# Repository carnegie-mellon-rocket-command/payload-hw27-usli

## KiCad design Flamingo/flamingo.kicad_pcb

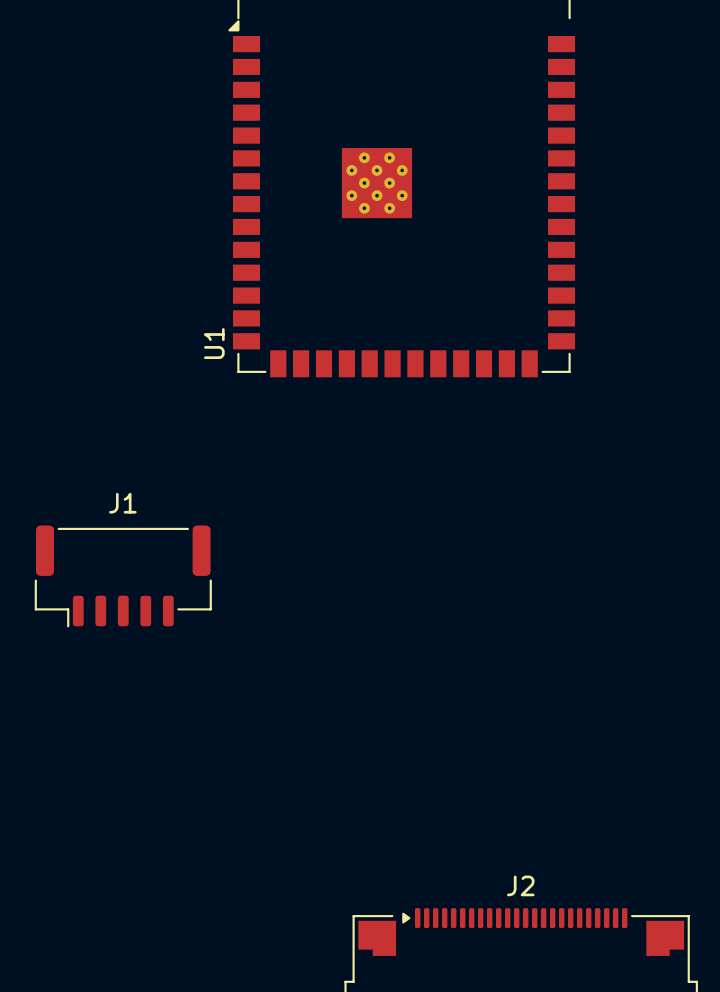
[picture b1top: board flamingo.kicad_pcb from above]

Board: 2 copper layers, 3 parts (0 on the bottom side), 19 nets, no tracks yet.

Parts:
J1: STA-M020X; JST_GH_BM05B-GHS-TBT_1x05-1MP_P1.25mm_Vertical
J2: Conn_01x24; Amphenol_F32Q-1A7x1-11024_1x24-1MP_P0.5mm_Horizontal
U1: ESP32-S3-WROOM-1-N16R8; ESP32-S3-WROOM-1

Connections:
/ESP32-S3 core/CAM_HREF: J2.9, U1.18 (IO10)
/ESP32-S3 core/CAM_PCLK: J2.17, U1.16 (IO46)
/ESP32-S3 core/CAM_RST: J2.6, U1.6 (IO6)
/ESP32-S3 core/CAM_SCL: J2.5, U1.5 (IO5)
/ESP32-S3 core/CAM_SDA: J2.3, U1.4 (IO4)
/ESP32-S3 core/CAM_VSYNC: J2.7, U1.17 (IO9)
/ESP32-S3 core/CAM_XCLK: J2.13, U1.21 (IO13)
/ESP32-S3 core/CAM_Y2: J2.19, U1.8 (IO15)
/ESP32-S3 core/CAM_Y3: J2.21, U1.9 (IO16)
/ESP32-S3 core/CAM_Y4: J2.22, U1.10 (IO17)
/ESP32-S3 core/CAM_Y5: J2.20, U1.11 (IO18)
/ESP32-S3 core/CAM_Y6: J2.18, U1.12 (IO8)
/ESP32-S3 core/CAM_Y7: J2.16, U1.13 (USB_D-)
/ESP32-S3 core/CAM_Y8: J2.14, U1.14 (USB_D+)
/ESP32-S3 core/CAM_Y9: J2.12, U1.15 (IO3)
/ESP32-S3 core/LASER_RX: J1.4, U1.38 (IO2)
/ESP32-S3 core/LASER_TX: J1.3, U1.39 (IO1)
GND: J1.1, J2.15
unnamed: U1.1 (GND), U1.40 (GND), U1.41 (GND)

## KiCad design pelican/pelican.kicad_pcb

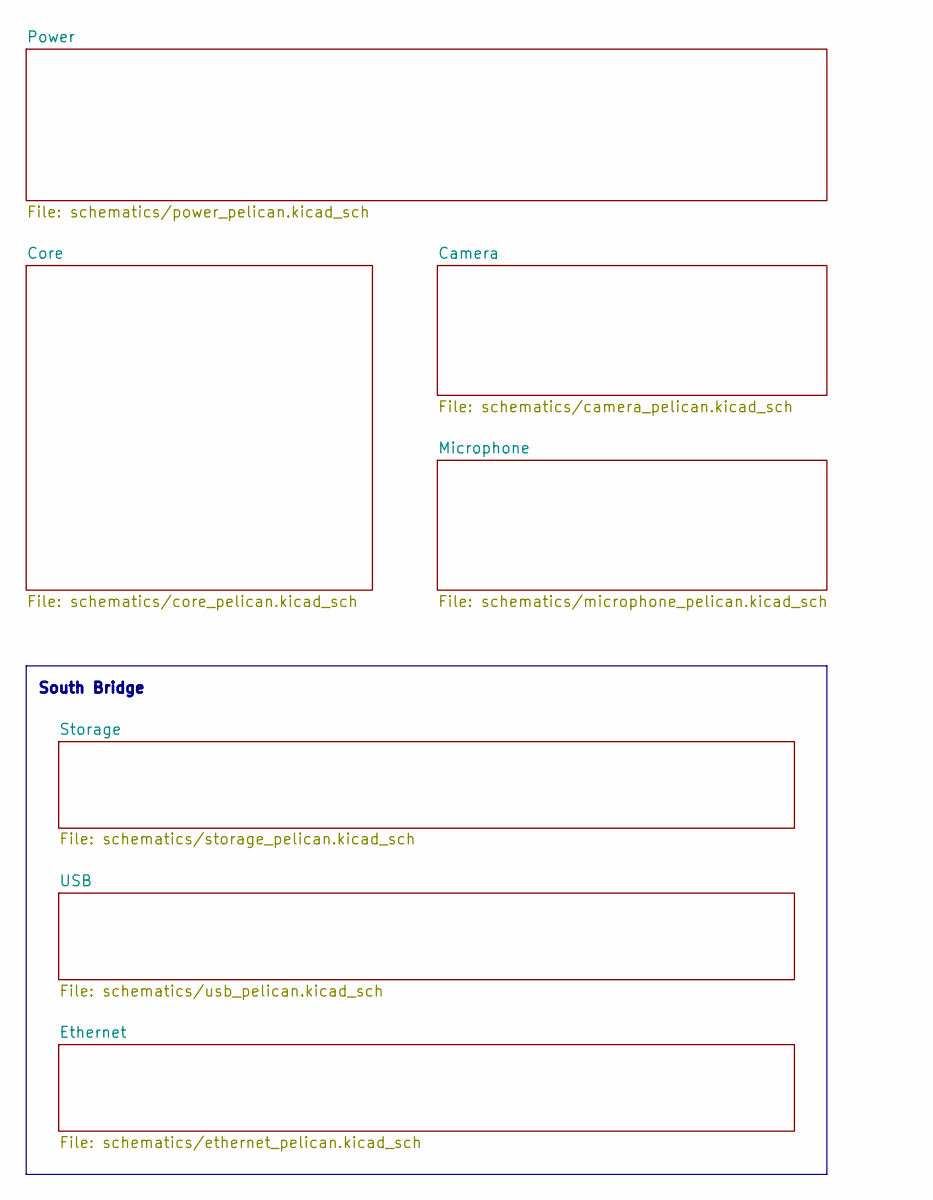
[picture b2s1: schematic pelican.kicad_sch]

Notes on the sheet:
South Bridge

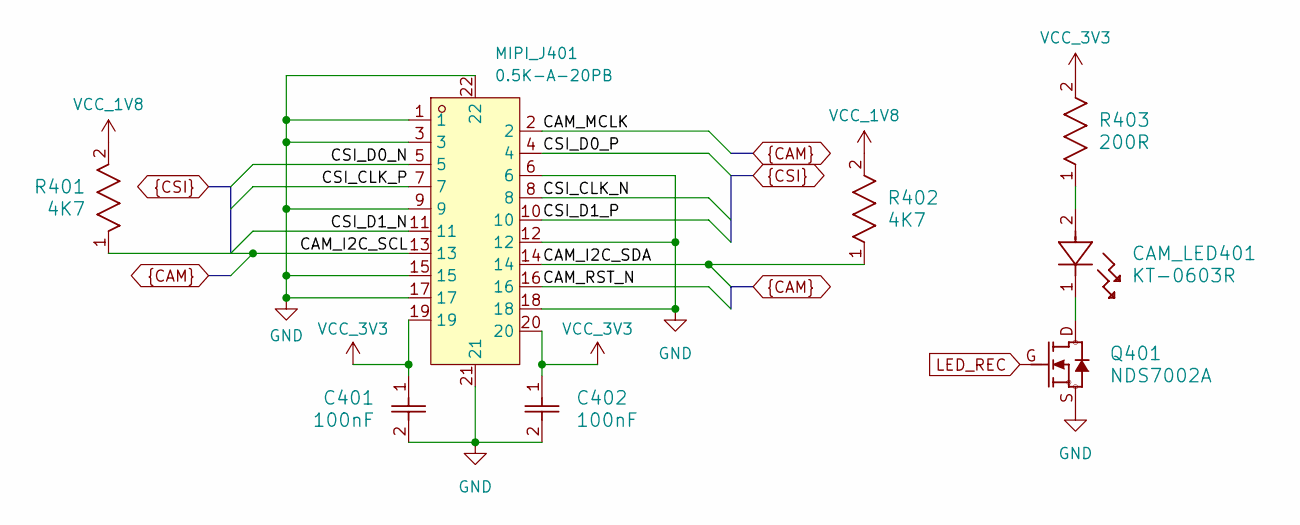
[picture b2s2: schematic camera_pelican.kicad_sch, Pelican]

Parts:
C401, C402: 100nF; C_GRM155R71C104KA88D; LCSC Part # C1525
CAM_LED401: KT-0603R; LED_LTST-C193KRKT-5A; LCSC Part # C2286
MIPI_J401: 0.5K-A-20PB; J_0.5K-A-20PB; MPN 0.5K-A-20PB; LCSC Part C2914144
Q401: NDS7002A; Q_NDS7002A; LCSC Part # C74715
R401, R402: 4K7; R_RC0402FR; LCSC Part # C25900
R403: 200R; R_RC0402FR; LCSC Part # C25087

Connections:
CAM_I2C_SCL: MIPI_J401.13, R401.1; also elsewhere on the board
CAM_I2C_SDA: MIPI_J401.14, R402.1; also elsewhere on the board
CAM_MCLK: MIPI_J401.2; also elsewhere on the board
CAM_RST_N: MIPI_J401.16; also elsewhere on the board
CSI_CLK_N: MIPI_J401.8; also elsewhere on the board
CSI_CLK_P: MIPI_J401.7; also elsewhere on the board
CSI_D0_N: MIPI_J401.5; also elsewhere on the board
CSI_D0_P: MIPI_J401.4; also elsewhere on the board
CSI_D1_N: MIPI_J401.11; also elsewhere on the board
CSI_D1_P: MIPI_J401.10; also elsewhere on the board
GND: C401.2, C402.2, MIPI_J401.1, MIPI_J401.3, MIPI_J401.6, MIPI_J401.9, MIPI_J401.12, MIPI_J401.15, MIPI_J401.17, MIPI_J401.18, MIPI_J401.21, MIPI_J401.22, Q401.S; also elsewhere on the board
LED_REC: Q401.G; also elsewhere on the board
unnamed: CAM_LED401.1, Q401.D
unnamed: CAM_LED401.2, R403.1
VCC_1V8: R401.2, R402.2; also elsewhere on the board
VCC_3V3: C401.1, C402.1, MIPI_J401.19, MIPI_J401.20, R403.2; also elsewhere on the board

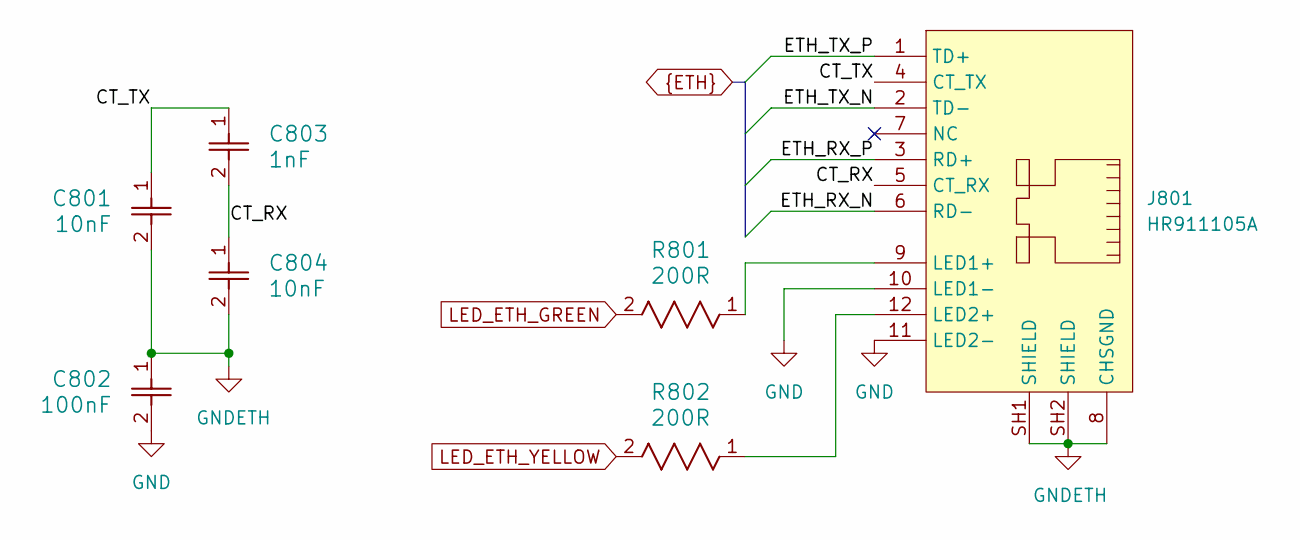
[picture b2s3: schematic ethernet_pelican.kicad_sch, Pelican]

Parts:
C801, C804: 10nF; C_CL05B103KO5NNNC; MPN CL05B103KO5NNNC; LCSC Part # C15195
C802: 100nF; C_GRM155R71C104KA88D; LCSC Part # C1525
C803: 1nF; C_CC0603CG100V102JN; MPN CC0603CG100V102JN; LCSC Part # C53084479
J801: HR911105A; J_HR911105A_TH; MPN HR911105A; LCSC Part C12074
R801, R802: 200R; R_RC0402FR; LCSC Part # C25087

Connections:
/Ethernet/CT_RX: C803.2, C804.1, J801.5 (CT_RX)
/Ethernet/CT_TX: C801.1, C803.1, J801.4 (CT_TX)
ETH_RX_N: J801.6 (RD-); also elsewhere on the board
ETH_RX_P: J801.3 (RD+); also elsewhere on the board
ETH_TX_N: J801.2 (TD-); also elsewhere on the board
ETH_TX_P: J801.1 (TD+); also elsewhere on the board
GND: C802.2, J801.10 (LED1-), J801.11 (LED2-); also elsewhere on the board
GNDETH: C801.2, C802.1, C804.2, J801.8 (CHSGND), J801.SH1 (SHIELD), J801.SH2 (SHIELD)
LED_ETH_GREEN: R801.2; also elsewhere on the board
LED_ETH_YELLOW: R802.2; also elsewhere on the board
unnamed: J801.9 (LED1+), R801.1
unnamed: J801.12 (LED2+), R802.1

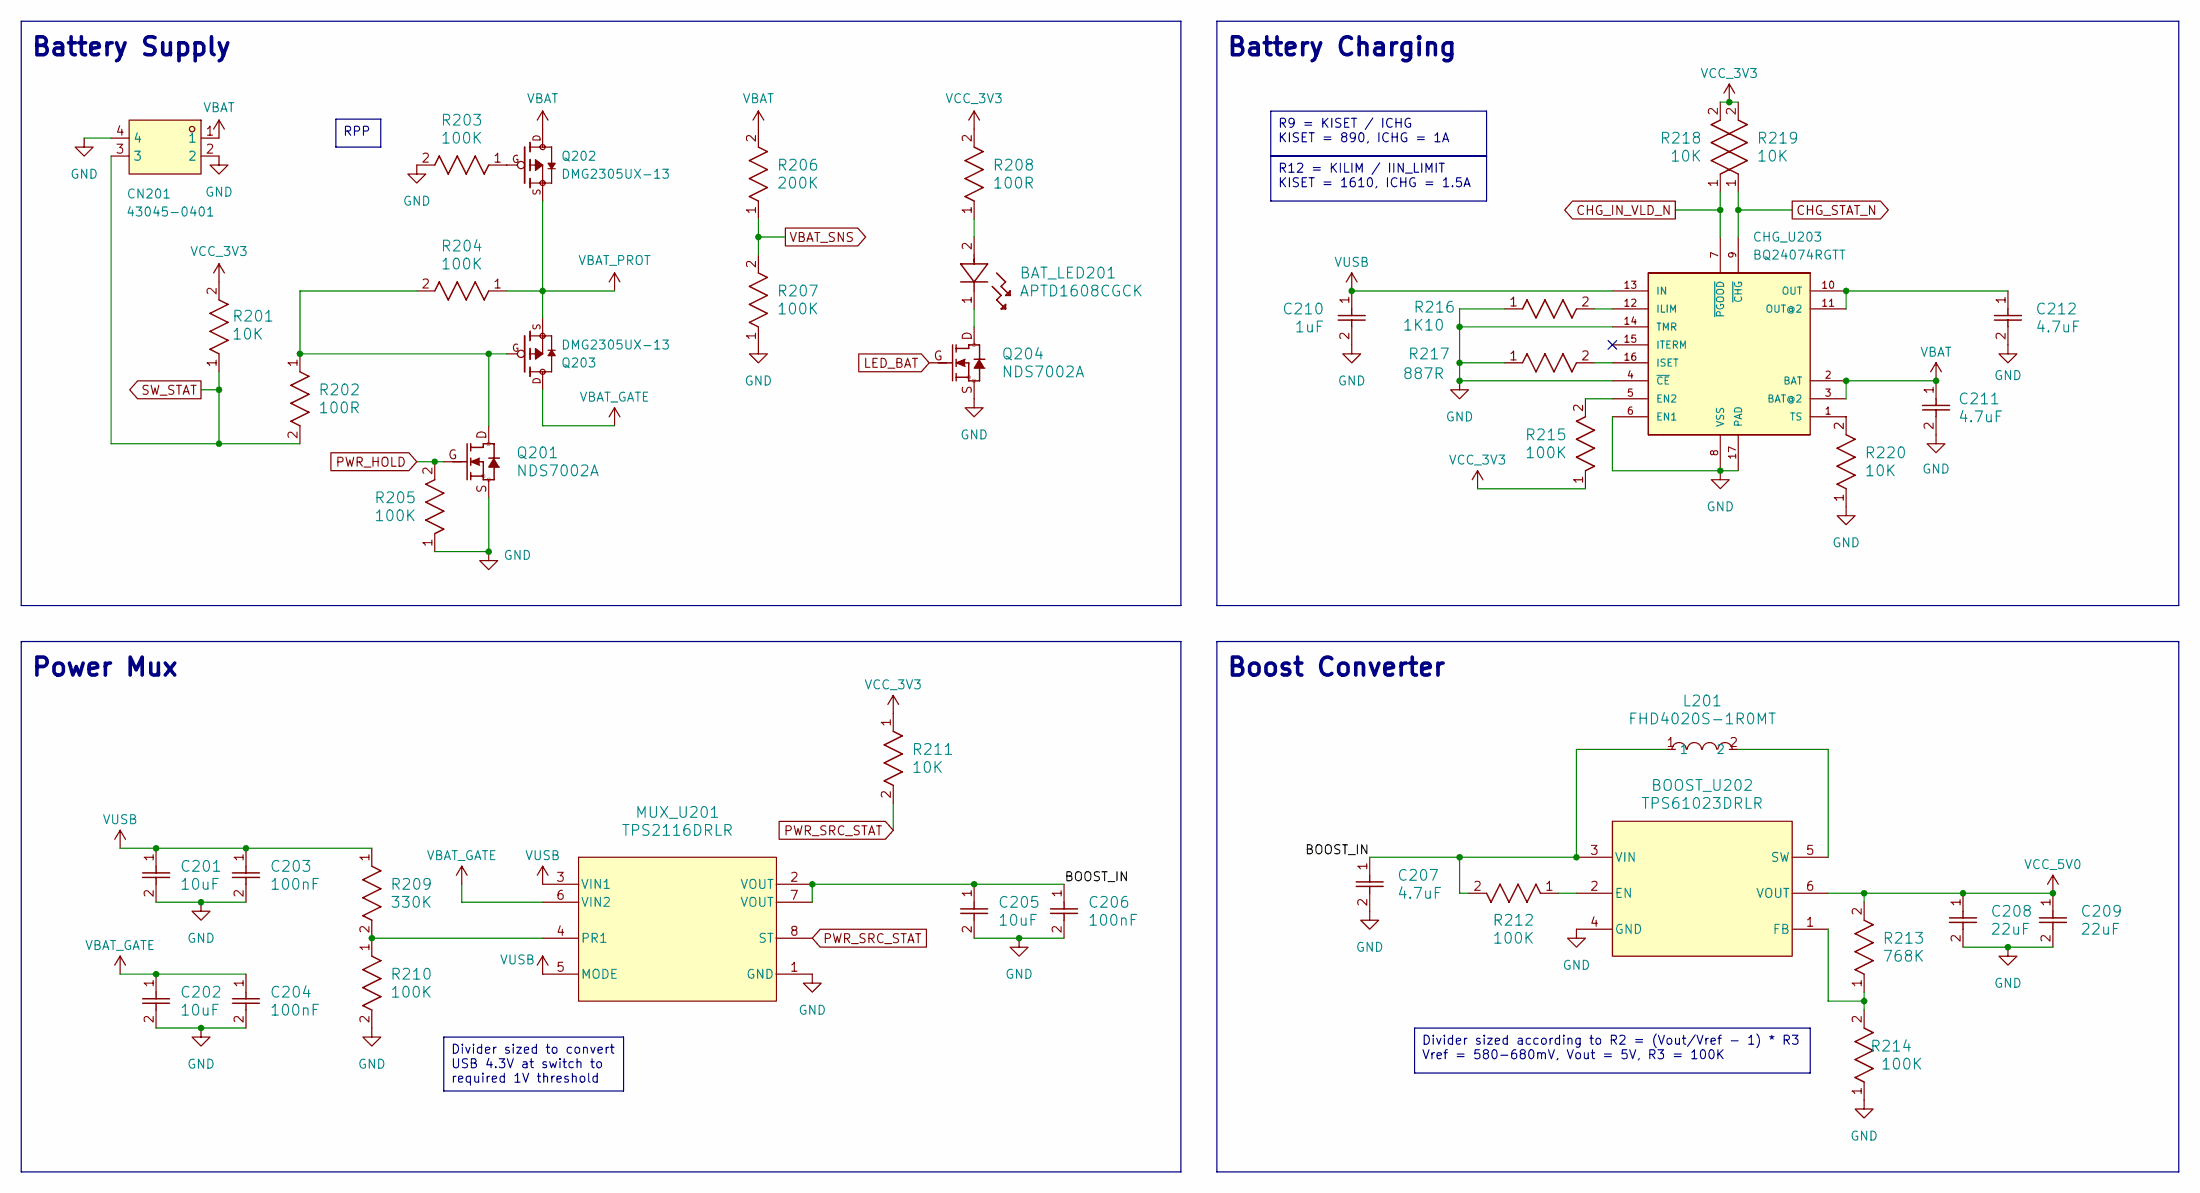
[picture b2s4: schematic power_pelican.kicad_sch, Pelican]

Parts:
BAT_LED201: APTD1608CGCK; LED_LTST-C193KGKT-5A; LCSC Part # C5121471
BOOST_U202: TPS61023DRLR; U_TPS61023DRLR; LCSC Part # C919459
C201, C202, C205: 10uF; C_GRM155R61A106ME11D; LCSC Part # C408132
C203, C204, C206: 100nF; C_GRM155R71C104KA88D; LCSC Part # C1525
C207, C211, C212: 4.7uF; C_GRM188R61A475KE15D; LCSC Part # C19666
C208, C209: 22uF; C_GRM188R61A226ME15D; LCSC Part # C84419
C210: 1uF; C_GRM155R61A105KE15D; LCSC Part # C52923
CHG_U203: BQ24074RGTT; U_BQ24074RGTT; LCSC Part # C2861252
CN201: 43045-0401; J_43045-0401_2x02_RA; MPN 430450401; LCSC Part C585880
L201: FHD4020S-1R0MT; L_FHD4020S-1R0MT; MPN FHD4020S-1R0MT; LCSC Part # C602028
MUX_U201: TPS2116DRLR; U_TPS2116DRLR; LCSC Part # C3235557
Q201, Q204: NDS7002A; Q_NDS7002A; LCSC Part # C74715
Q202, Q203: DMG2305UX-13; Q_DMG2305UX-13; PARTREV 09/2018; LCSC Part # C144153
R201, R211, R218, R219, R220: 10K; R_RC0402FR; LCSC Part # C25744
R202, R208: 100R; R_RC0402FR; LCSC Part # C25076
R203, R204, R205, R207, R210, R212, R214, R215: 100K; R_RC0402FR; LCSC Part # C25741
R206: 200K; R_RC0402FR; LCSC Part # C25764
R209: 330K; R_RC0402FR; LCSC Part # C25778
R213: 768K; R_RC0402FR; LCSC Part # C273722
R216: 1K10; R_RC0402FR; LCSC Part # C25860
R217: 887R; R_RC0402FR; LCSC Part # C477810

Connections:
/Power/BOOST_IN: BOOST_U202.3 (VIN), C205.1, C206.1, C207.1, L201.1, MUX_U201.2 (VOUT), MUX_U201.7 (VOUT), R212.2
CHG_IN_VLD_N: CHG_U203.7 (~PGOOD), R218.1; also elsewhere on the board
CHG_STAT_N: CHG_U203.9 (~CHG), R219.1; also elsewhere on the board
GND: BOOST_U202.4 (GND), C201.2, C202.2, C203.2, C204.2, C205.2, C206.2, C207.2, C208.2, C209.2, C210.2, C211.2, C212.2, CHG_U203.4 (~CE), CHG_U203.6 (EN1), CHG_U203.8 (VSS), CHG_U203.14 (TMR), CHG_U203.17 (PAD), CN201.2, CN201.4, MUX_U201.1 (GND), Q201.S, Q204.S, R203.2, R205.1, R207.1, R210.2, R214.1, R216.1, R217.1, R220.1; also elsewhere on the board
LED_BAT: Q204.G; also elsewhere on the board
unnamed: BAT_LED201.1, Q204.D
unnamed: BAT_LED201.2, R208.1
unnamed: BOOST_U202.2 (EN), R212.1
unnamed: BOOST_U202.1 (FB), R213.1, R214.2
unnamed: BOOST_U202.5 (SW), L201.2
unnamed: CHG_U203.5 (EN2), R215.2
unnamed: CHG_U203.12 (ILIM), R216.2
unnamed: CHG_U203.16 (ISET), R217.2
unnamed: C212.1, CHG_U203.10 (OUT), CHG_U203.11 (OUT@2)
unnamed: CHG_U203.1 (TS), R220.2
unnamed: MUX_U201.4 (PR1), R209.2, R210.1
unnamed: Q201.D, Q203.G, R202.1, R204.2
unnamed: Q202.G, R203.1
unnamed: Q202.S, Q203.S, R204.1
PWR_HOLD: Q201.G, R205.2; also elsewhere on the board
PWR_SRC_STAT: MUX_U201.8 (ST), R211.2; also elsewhere on the board
SW_STAT: CN201.3, R201.1, R202.2; also elsewhere on the board
VBAT: C211.1, CHG_U203.2 (BAT), CHG_U203.3 (BAT@2), CN201.1, Q202.D, R206.2
VBAT_SNS: R206.1, R207.2; also elsewhere on the board
VCC_3V3: R201.2, R208.2, R211.1, R215.1, R218.2, R219.2; also elsewhere on the board
VCC_5V0: BOOST_U202.6 (VOUT), C208.1, C209.1, R213.2; also elsewhere on the board
VUSB: C201.1, C203.1, C210.1, CHG_U203.13 (IN), MUX_U201.3 (VIN1), MUX_U201.5 (MODE), R209.1; also elsewhere on the board

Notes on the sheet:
Battery Charging
Power Mux
Battery Supply
Boost Converter
Divider sized according to R2 = (Vout/Vref - 1) * R3 Vref = 580-680mV, Vout = 5V, R3 = 100K
R12 = KILIM / IIN_LIMIT KISET = 1610, ICHG = 1.5A
R9 = KISET / ICHG KISET = 890, ICHG = 1A
Divider sized to convert USB 4.3V at switch to required 1V threshold
RPP

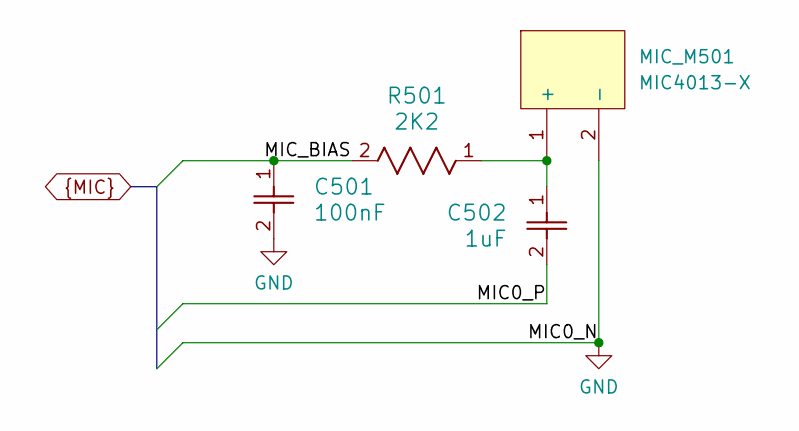
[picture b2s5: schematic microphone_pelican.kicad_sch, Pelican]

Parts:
C501: 100nF; C_GRM155R71C104KA88D; LCSC Part # C1525
C502: 1uF; C_GRM155R61A105KE15D; LCSC Part # C52923
MIC_M501: MIC4013-X; M_MIC4013-X; MPN MIC4013-X; LCSC Part # C49118137
R501: 2K2; R_RC0402FR; LCSC Part # C25879

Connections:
GND: C501.2, MIC_M501.2 (-); also elsewhere on the board
MIC0_P: C502.2; also elsewhere on the board
MIC_BIAS: C501.1, R501.2; also elsewhere on the board
unnamed: C502.1, MIC_M501.1 (+), R501.1

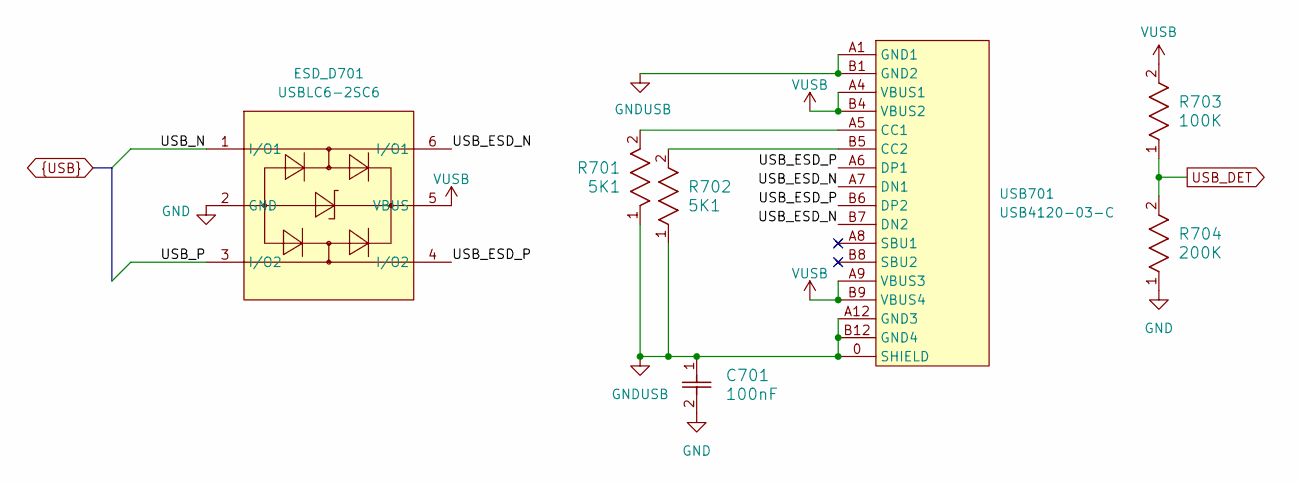
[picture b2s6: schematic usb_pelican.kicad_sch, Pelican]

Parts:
C701: 100nF; C_GRM155R71C104KA88D; LCSC Part # C1525
ESD_D701: USBLC6-2SC6; D_USBLC6-2SC6; MPN USBLC6-2SC6; LCSC Part # C7519
R701, R702: 5K1; R_RC0402FR; LCSC Part # C25905
R703: 100K; R_RC0402FR; LCSC Part # C25741
R704: 200K; R_RC0402FR; LCSC Part # C25764
USB701: USB4120-03-C; J_USB4120-03-C_SMD; MPN USB4120-03-C; LCSC Part C3445864

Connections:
/USB/USB_ESD_N: ESD_D701.6 (I/O1), USB701.A7 (DN1), USB701.B7 (DN2)
/USB/USB_ESD_P: ESD_D701.4 (I/O2), USB701.A6 (DP1), USB701.B6 (DP2)
GND: C701.2, ESD_D701.2 (GND), R704.1; also elsewhere on the board
GNDUSB: C701.1, R701.1, R702.1, USB701.0 (SHIELD), USB701.A1 (GND1), USB701.A12 (GND3), USB701.B1 (GND2), USB701.B12 (GND4)
unnamed: R701.2, USB701.A5 (CC1)
unnamed: R702.2, USB701.B5 (CC2)
USB_DET: R703.1, R704.2; also elsewhere on the board
USB_N: ESD_D701.1 (I/O1); also elsewhere on the board
USB_P: ESD_D701.3 (I/O2); also elsewhere on the board
VUSB: ESD_D701.5 (VBUS), R703.2, USB701.A4 (VBUS1), USB701.A9 (VBUS3), USB701.B4 (VBUS2), USB701.B9 (VBUS4); also elsewhere on the board

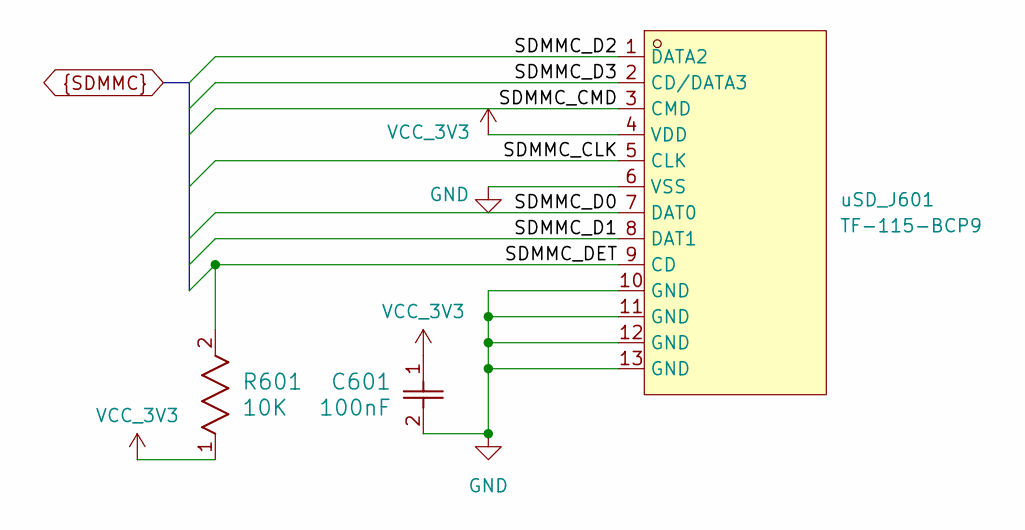
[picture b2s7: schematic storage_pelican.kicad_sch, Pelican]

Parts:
C601: 100nF; C_GRM155R71C104KA88D; LCSC Part # C1525
R601: 10K; R_RC0402FR; LCSC Part # C25744
uSD_J601: TF-115-BCP9; J_TF-115-BCP9; MPN TF-115-BCP9; LCSC Part # C720505

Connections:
GND: C601.2, uSD_J601.6 (VSS), uSD_J601.10 (GND), uSD_J601.11 (GND), uSD_J601.12 (GND), uSD_J601.13 (GND); also elsewhere on the board
SDMMC_CLK: uSD_J601.5 (CLK); also elsewhere on the board
SDMMC_CMD: uSD_J601.3 (CMD); also elsewhere on the board
SDMMC_D0: uSD_J601.7 (DAT0); also elsewhere on the board
SDMMC_D1: uSD_J601.8 (DAT1); also elsewhere on the board
SDMMC_D2: uSD_J601.1 (DATA2); also elsewhere on the board
SDMMC_D3: uSD_J601.2 (CD/DATA3); also elsewhere on the board
SDMMC_DET: R601.2, uSD_J601.9 (CD); also elsewhere on the board
VCC_3V3: C601.1, R601.1, uSD_J601.4 (VDD); also elsewhere on the board

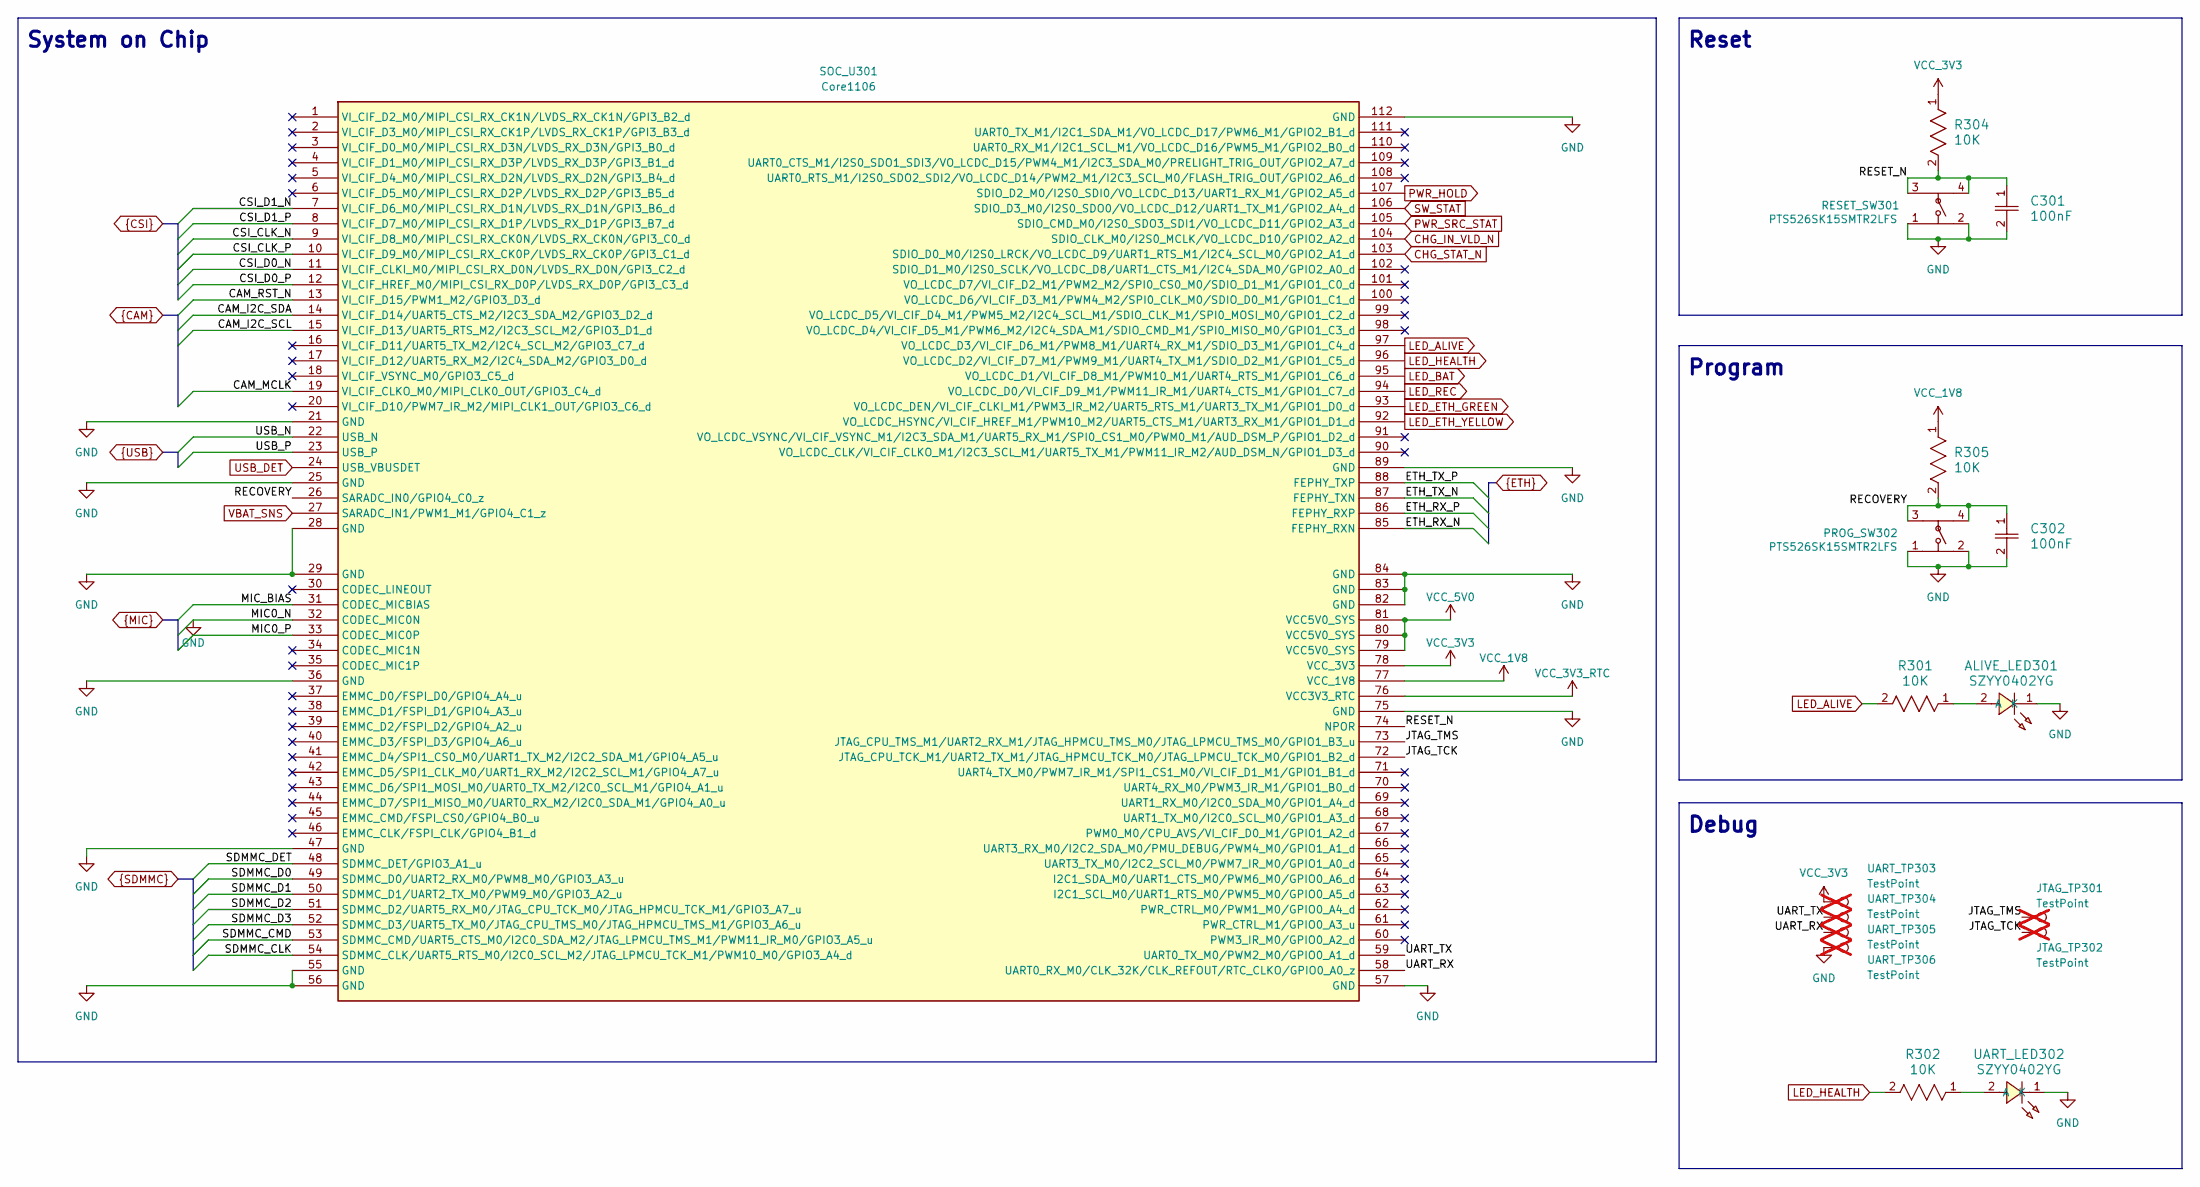
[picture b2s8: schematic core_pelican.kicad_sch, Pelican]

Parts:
ALIVE_LED301: SZYY0402YG; LED_SZYY0402YG; MPN SZYY0402YG; LCSC Part # C434449
C301, C302: 100nF; C_GRM155R71C104KA88D; LCSC Part # C1525
JTAG_TP301, JTAG_TP302: TestPoint; TestPoint_Pad_D1.5mm; not fitted
PROG_SW302: PTS526SK15SMTR2LFS; SW_PTS526SK15SMTR2LFS; LCSC Part # C2689521
R301, R302, R304, R305: 10K; R_RC0402FR; LCSC Part # C25744
RESET_SW301: PTS526SK15SMTR2LFS; SW_PTS526SK15SMTR2LFS; LCSC Part # C2689521
SOC_U301: Core1106; P_Core1106
UART_LED302: SZYY0402YG; LED_SZYY0402YG; MPN SZYY0402YG; LCSC Part # C434449
UART_TP303, UART_TP304, UART_TP305, UART_TP306: TestPoint; TestPoint_Pad_D1.5mm; not fitted

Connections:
/Core/JTAG_TCK: JTAG_TP302.1 (1_1), SOC_U301.72 (JTAG_CPU_TCK_M1/UART2_TX_M1/JTAG_HPMCU_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)
/Core/JTAG_TMS: JTAG_TP301.1 (1_1), SOC_U301.73 (JTAG_CPU_TMS_M1/UART2_RX_M1/JTAG_HPMCU_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)
/Core/RECOVERY: C302.1, PROG_SW302.3, PROG_SW302.4, R305.2, SOC_U301.26 (SARADC_IN0/GPIO4_C0_z)
/Core/RESET_N: C301.1, R304.2, RESET_SW301.3, RESET_SW301.4, SOC_U301.74 (NPOR)
/Core/UART_RX: SOC_U301.58 (UART0_RX_M0/CLK_32K/CLK_REFOUT/RTC_CLKO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), UART_TP305.1 (1_1)
/Core/UART_TX: SOC_U301.59 (UART0_TX_M0/PWM2_M0/GPIO0_A1_d), UART_TP304.1 (1_1)
CAM_I2C_SCL: SOC_U301.15 (VI_CIF_D13/UART5_RTS_M2/I2C3_SCL_M2/GPI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); also elsewhere on the board
CAM_I2C_SDA: SOC_U301.14 (VI_CIF_D14/UART5_CTS_M2/I2C3_SDA_M2/GPI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); also elsewhere on the board
CAM_MCLK: SOC_U301.19 (VI_CIF_CLKO_M0/MIPI_CLK0_OUT/GPIO3_C4_d); also elsewhere on the board
CAM_RST_N: SOC_U301.13 (VI_CIF_D15/PWM1_M2/GPIO3_D3_d); also elsewhere on the board
CHG_IN_VLD_N: SOC_U301.104 (SDIO_CLK_M0/I2S0_MCLK/VO_LCDC_D10/GPIO2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); also elsewhere on the board
CHG_STAT_N: SOC_U301.103 (SDIO_D0_M0/I2S0_LRCK/VO_LCDC_D9/UART1_R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); also elsewhere on the board
CSI_CLK_N: SOC_U301.9 (VI_CIF_D8_M0/MIPI_CSI_RX_CK0N/LVDS_RX_C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); also elsewhere on the board
CSI_CLK_P: SOC_U301.10 (VI_CIF_D9_M0/MIPI_CSI_RX_CK0P/LVDS_RX_C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); also elsewhere on the board
CSI_D0_N: SOC_U301.11 (VI_CIF_CLKI_M0/MIPI_CSI_RX_D0N/LVDS_RX_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); also elsewhere on the board
CSI_D0_P: SOC_U301.12 (VI_CIF_HREF_M0/MIPI_CSI_RX_D0P/LVDS_RX_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); also elsewhere on the board
CSI_D1_N: SOC_U301.7 (VI_CIF_D6_M0/MIPI_CSI_RX_D1N/LVDS_RX_D1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); also elsewhere on the board
CSI_D1_P: SOC_U301.8 (VI_CIF_D7_M0/MIPI_CSI_RX_D1P/LVDS_RX_D1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); also elsewhere on the board
ETH_RX_N: SOC_U301.85 (FEPHY_RXN); also elsewhere on the board
ETH_RX_P: SOC_U301.86 (FEPHY_RXP); also elsewhere on the board
ETH_TX_N: SOC_U301.87 (FEPHY_TXN); also elsewhere on the board
ETH_TX_P: SOC_U301.88 (FEPHY_TXP); also elsewhere on the board
GND: ALIVE_LED301.1 (K), C301.2, C302.2, PROG_SW302.1, PROG_SW302.2, RESET_SW301.1, RESET_SW301.2, SOC_U301.21 (GND), SOC_U301.25 (GND), SOC_U301.28 (GND), SOC_U301.29 (GND), SOC_U301.32 (CODEC_MIC0N), SOC_U301.36 (GND), SOC_U301.47 (GND), SOC_U301.55 (GND), SOC_U301.56 (GND), SOC_U301.57 (GND), SOC_U301.75 (GND), SOC_U301.82 (GND), SOC_U301.83 (GND), SOC_U301.84 (GND), SOC_U301.89 (GND), SOC_U301.112 (GND), UART_LED302.1 (K), UART_TP306.1 (1_1); also elsewhere on the board
LED_ALIVE: R301.2, SOC_U301.97 (VO_LCDC_D3/VI_CIF_D6_M1/PWM8_M1/UART4_R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)
LED_BAT: SOC_U301.95 (VO_LCDC_D1/VI_CIF_D8_M1/PWM10_M1/UART4_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); also elsewhere on the board
LED_ETH_GREEN: SOC_U301.93 (VO_LCDC_DEN/VI_CIF_CLKI_M1/PWM3_IR_M2/U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); also elsewhere on the board
LED_ETH_YELLOW: SOC_U301.92 (VO_LCDC_HSYNC/VI_CIF_HREF_M1/PWM10_M2/U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); also elsewhere on the board
LED_HEALTH: R302.2, SOC_U301.96 (VO_LCDC_D2/VI_CIF_D7_M1/PWM9_M1/UART4_T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)
LED_REC: SOC_U301.94 (VO_LCDC_D0/VI_CIF_D9_M1/PWM11_IR_M1/UAR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); also elsewhere on the board
MIC0_P: SOC_U301.33 (CODEC_MIC0P); also elsewhere on the board
MIC_BIAS: SOC_U301.31 (CODEC_MICBIAS); also elsewhere on the board
unnamed: ALIVE_LED301.2 (A), R301.1
unnamed: R302.1, UART_LED302.2 (A)
PWR_HOLD: SOC_U301.107 (SDIO_D2_M0/I2S0_SDI0/VO_LCDC_D13/UART1_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); also elsewhere on the board
PWR_SRC_STAT: SOC_U301.105 (SDIO_CMD_M0/I2S0_SDO3_SDI1/VO_LCDC_D11/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); also elsewhere on the board
SDMMC_CLK: SOC_U301.54 (SDMMC_CLK/UART5_RTS_M0/I2C0_SCL_M2/JTAG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); also elsewhere on the board
SDMMC_CMD: SOC_U301.53 (SDMMC_CMD/UART5_CTS_M0/I2C0_SDA_M2/JTAG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); also elsewhere on the board
SDMMC_D0: SOC_U301.49 (SDMMC_D0/UART2_RX_M0/PWM8_M0/GPIO3_A3_u); also elsewhere on the board
SDMMC_D1: SOC_U301.50 (SDMMC_D1/UART2_TX_M0/PWM9_M0/GPIO3_A2_u); also elsewhere on the board
SDMMC_D2: SOC_U301.51 (SDMMC_D2/UART5_RX_M0/JTAG_CPU_TCK_M0/JT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); also elsewhere on the board
SDMMC_D3: SOC_U301.52 (SDMMC_D3/UART5_TX_M0/JTAG_CPU_TMS_M0/JT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); also elsewhere on the board
SDMMC_DET: SOC_U301.48 (SDMMC_DET/GPIO3_A1_u); also elsewhere on the board
SW_STAT: SOC_U301.106 (SDIO_D3_M0/I2S0_SDO0/VO_LCDC_D12/UART1_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); also elsewhere on the board
USB_DET: SOC_U301.24 (USB_VBUSDET); also elsewhere on the board
USB_N: SOC_U301.22 (USB_N); also elsewhere on the board
USB_P: SOC_U301.23 (USB_P); also elsewhere on the board
VBAT_SNS: SOC_U301.27 (SARADC_IN1/PWM1_M1/GPIO4_C1_z); also elsewhere on the board
VCC_1V8: R305.1, SOC_U301.77 (VCC_1V8); also elsewhere on the board
VCC_3V3: R304.1, SOC_U301.78 (VCC_3V3), UART_TP303.1 (1_1); also elsewhere on the board
VCC_3V3_RTC: SOC_U301.76 (VCC3V3_RTC)
VCC_5V0: SOC_U301.79 (VCC5V0_SYS), SOC_U301.80 (VCC5V0_SYS), SOC_U301.81 (VCC5V0_SYS); also elsewhere on the board

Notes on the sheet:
Debug
System on Chip
Program
Reset

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
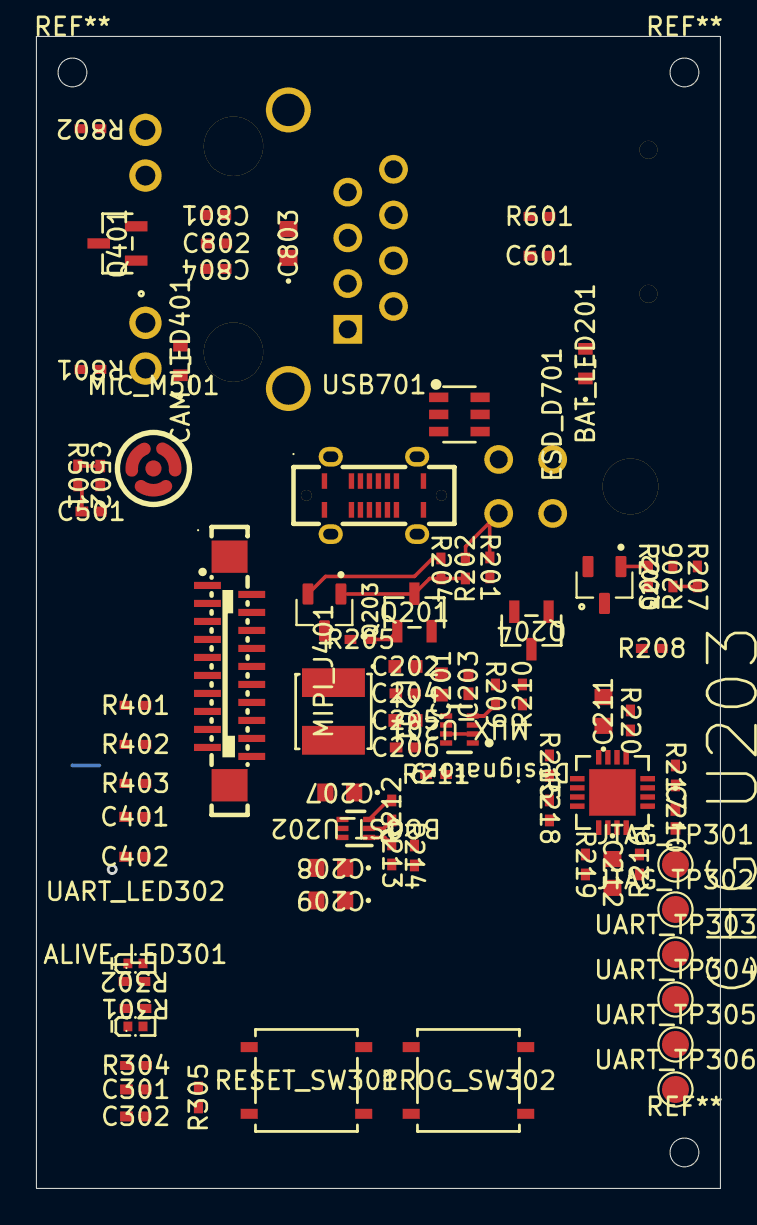
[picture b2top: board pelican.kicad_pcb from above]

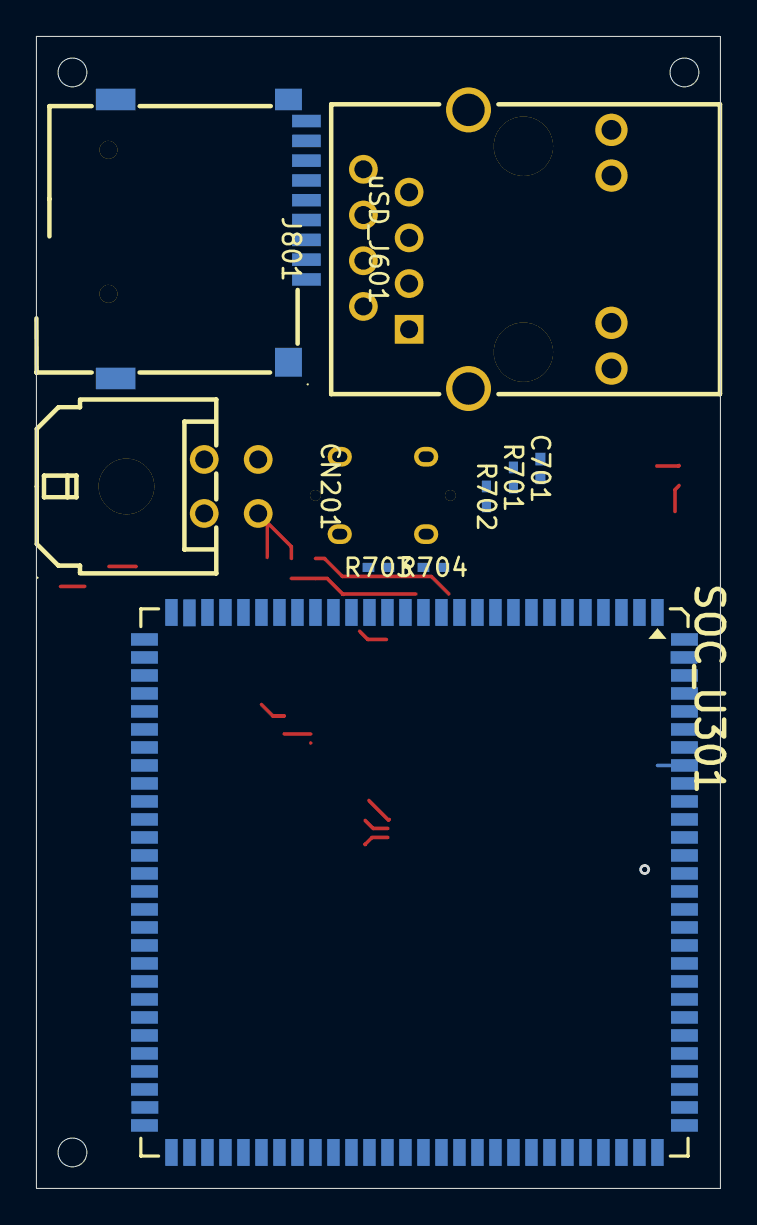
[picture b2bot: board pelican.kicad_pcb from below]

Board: 4 copper layers, 38.0 x 64.0 mm, 88 parts (9 on the bottom side), 82 nets.
